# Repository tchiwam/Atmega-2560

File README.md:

# Atmega-2560
Derivative work from the orginal Arduino MEGA 2650 R3 Creative Commons Attribution Share-Alike

# The why
I was simply flexing my kicad skills with the latest version 5.0.0

# The long term goal
This will be the start of a series of adapted Atmega2650 boards for various purposes.

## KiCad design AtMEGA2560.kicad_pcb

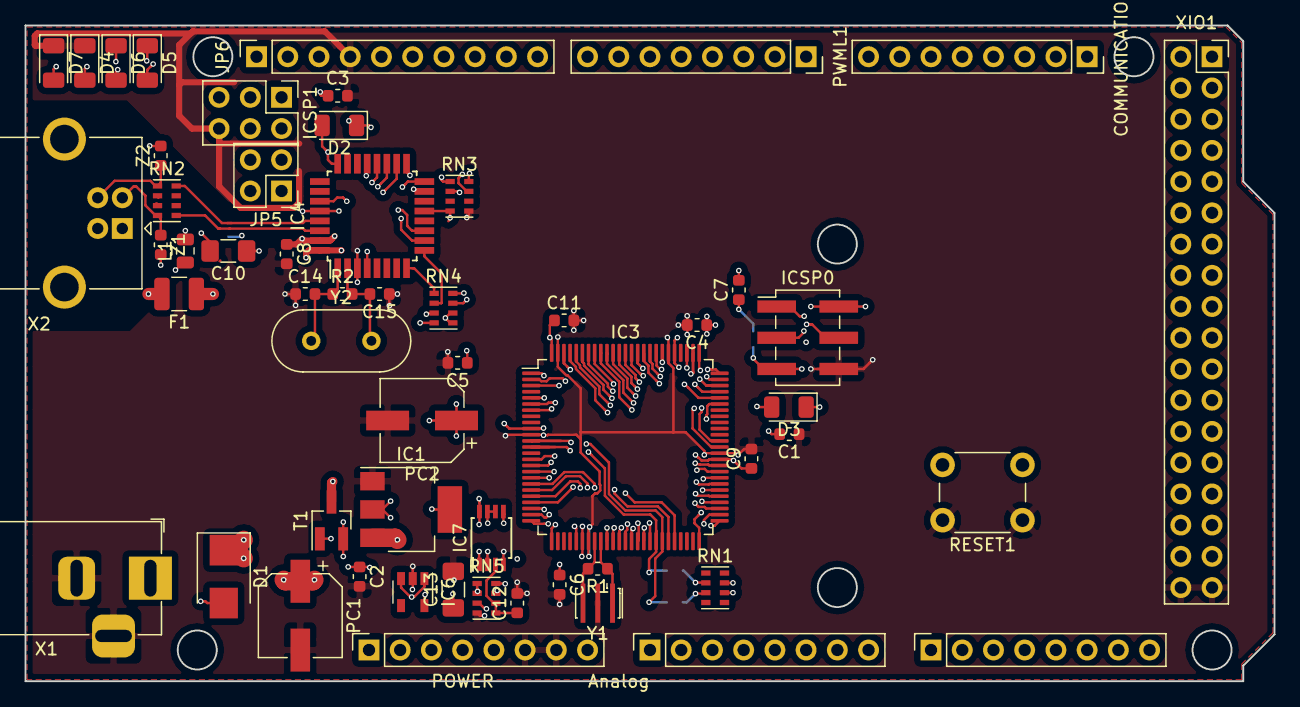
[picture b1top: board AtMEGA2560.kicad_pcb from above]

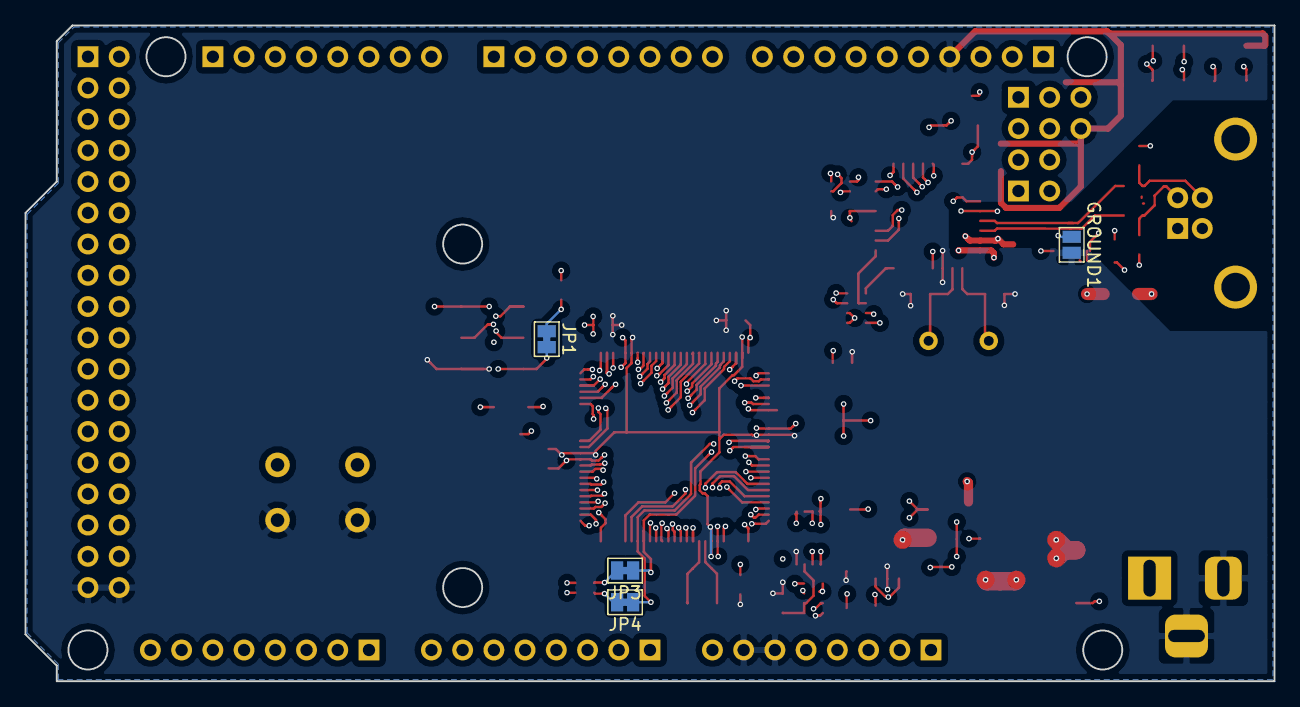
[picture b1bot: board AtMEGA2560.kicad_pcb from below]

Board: 4 copper layers, 101.6 x 53.3 mm, 60 parts (4 on the bottom side), 113 nets.

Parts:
ADCH1: Conn_01x08; PinSocket_1x08_P2.54mm_Vertical
ADCL1: Conn_01x08; PinSocket_1x08_P2.54mm_Vertical
C1, C14, C15: 22pF; C_0603_1608Metric
C2, C4, C5, C6: 100n; C_0603_1608Metric
C3, C7, C8, C9, C11, C12: 100nF; C_0603_1608Metric
C10, C13: 1uF; C_1206_3216Metric_Pad1.42x1.75mm_HandSolder
COMMUNICATION1: Conn_01x08; PinSocket_1x08_P2.54mm_Vertical
D1: M7; D_SMB
D2, D3: CD1206-S01575; D_1206_3216Metric
D4: YEL; LED_1206_3216Metric
D5: RX YELLOW; LED_1206_3216Metric
D6: TX YELLOW; LED_1206_3216Metric
D7: GRN; LED_1206_3216Metric
F1: MF-MSMF050-2 500mA; Fuse_1210_3225Metric
GROUND1: SolderJumper_2_Open; SolderJumper-2_P1.3mm_Open_Pad1.0x1.5mm
IC1: NCP1117-5.0_SOT223; SOT-223-3_TabPin2
IC3: ATmega2560-16AU; TQFP-100_14x14mm_P0.5mm
IC4: ATmega16U2-AU; TQFP-32_7x7mm_P0.8mm
IC6: LP2985-3.3; SOT-23-5
IC7: LMV358IDGKR; TSSOP-8_3x3mm_P0.65mm
ICSP0: Conn_02x03_Odd_Even; PinHeader_2x03_P2.54mm_Vertical_SMD
ICSP1: Conn_02x03_Odd_Even; PinHeader_2x03_P2.54mm_Vertical
JP1: RESET-EN; SolderJumper-2_P1.3mm_Bridged_Pad1.0x1.5mm
JP3, JP4: SolderJumper_2_Bridged; SolderJumper-2_P1.3mm_Bridged_Pad1.0x1.5mm
JP5: Conn_02x02_Odd_Even; PinHeader_2x02_P2.54mm_Vertical
JP6: Conn_01x10; PinSocket_1x10_P2.54mm_Vertical
L1: BLM21; L_0805_2012Metric
PC1: CP; CP_Elec_6.3x5.4
PC2: 47u; CP_Elec_6.3x5.4
POWER1: Conn_01x08; PinSocket_1x08_P2.54mm_Vertical
PWML1: Conn_01x08; PinSocket_1x08_P2.54mm_Vertical
R1, R2: 1M; R_0603_1608Metric
RESET1: SW_Push; SW_PUSH_6mm
RN1, RN5: 10k; R_Cat16-4
RN2: 22R; R_Cat16-4
RN3, RN4: 1k; R_Cat16-4
T1: FDN340P; SOT-23_Handsoldering
X1: DC21MMX; BarrelJack_Horizontal
X2: USB-B_TH; USB_B_OST_USB-B1HSxx_Horizontal
XIO1: Conn_02x18_Odd_Even; PinSocket_2x18_P2.54mm_Vertical
Y1: CSTCE16M0V53-R0 16MHZ; Resonator_SMD_muRata_CSTxExxV-3Pin_3.0x1.1mm_HandSoldering
Y2: 16MHz; Crystal_HC18-U_Vertical
Z1, Z2: CG0603MLC-05E; R_0603_1608Metric

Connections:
+3V3: C13.1, IC6.5, IC7.2, POWER1.4
+5V: C4.1, C5.1, C6.1, C9.1, C11.1, D2.1, D3.1, IC1.2, IC3.10, IC3.31, IC3.61, IC3.80, IC3.100, IC4.4, IC4.32, IC6.1, IC6.3, IC7.8, ICSP0.2, ICSP1.2, PC2.1, POWER1.2, POWER1.5, RN1.6, RN1.7, RN3.1, RN4.5, RN4.6, RN5.1, RN5.2, T1.2, XIO1.1, XIO1.2
+VDC: C2.1, D1.1, IC1.3, PC1.1, POWER1.8, RN5.3
/8PB4: IC4.18, JP5.1
/8PB5: IC4.19, JP5.3
/8PB6: IC4.20, JP5.2
/8PB7: IC4.21, JP5.4
/ADC0: ADCL1.1, IC3.97
/ADC1: ADCL1.2, IC3.96
/ADC2: ADCL1.3, IC3.95
/ADC3: ADCL1.4, IC3.94
/ADC4: ADCL1.5, IC3.93
/ADC5: ADCL1.6, IC3.92
/ADC6: ADCL1.7, IC3.91
/ADC7: ADCL1.8, IC3.90
/ADC8: ADCH1.1, IC3.89
/ADC9: ADCH1.2, IC3.88
/ADC10: ADCH1.3, IC3.87
/ADC11: ADCH1.4, IC3.86
/ADC12: ADCH1.5, IC3.85
/ADC13: ADCH1.6, IC3.84
/ADC14: ADCH1.7, IC3.83
/ADC15: ADCH1.8, IC3.82
/MISO2: IC4.17, ICSP1.1
/MOSI2: IC4.16, ICSP1.4
/PB4: IC3.23, JP6.8
/PB5: IC3.24, JP6.7
/PB6: IC3.25, JP6.6
/PC0: IC3.53, XIO1.17
/PC1: IC3.54, XIO1.18
/PC2: IC3.55, XIO1.15
/PC3: IC3.56, XIO1.16
/PC4: IC3.57, XIO1.13
/PC5: IC3.58, XIO1.14
/PC6: IC3.59, XIO1.11
/PC7: IC3.60, XIO1.12
/PE3: IC3.5, PWML1.6
/PE4: IC3.6, PWML1.3
/PE5: IC3.7, PWML1.4
/RXD1: COMMUNICATION1.3, IC3.45
/SCK2: IC4.15, ICSP1.3
/TXD1: COMMUNICATION1.4, IC3.46
/USB1+: IC4.29, RN2.8
/USB1-: IC4.30, RN2.5
/USB2+: RN2.1, X2.3, Z2.1
/USB2-: RN2.4, X2.2, Z1.1
/USBGND: C10.2, GROUND1.1, IC4.28, L1.2, X2.4
/USBSHIELD: L1.1, X2.5, Z1.2, Z2.2
/VBUS: F1.2, X2.1
/XTAL1: IC3.34, R1.1, Y1.1
/XTAL2: IC3.33, R1.2, Y1.3
AREF: C3.1, IC3.98, JP6.3
GND: C1.1, C2.2, C3.2, C4.2, C5.2, C6.2, C8.2, C9.2, C11.2, C12.2, C13.2, C14.1, C15.1, D4.1, D7.1, GROUND1.2, IC1.1, IC3.11, IC3.32, IC3.62, IC3.81, IC3.99, IC4.3, IC6.2, IC7.4, ICSP0.6, ICSP1.6, JP6.4, PC1.2, PC2.2, POWER1.6, POWER1.7, RESET1.1, RN3.5, RN5.4, X1.2, X1.3, XIO1.35, XIO1.36, Y1.2
MISO: IC3.22, ICSP0.1, XIO1.32
MOSI: IC3.21, ICSP0.4, XIO1.31
unnamed: C7.1, JP1.1
unnamed: C10.1, IC4.27
unnamed: C12.1, IC7.3, RN5.5, RN5.6
unnamed: C14.2, IC4.1, R2.1, Y2.1
unnamed: C15.2, IC4.2, R2.2, Y2.2
unnamed: D1.2, X1.1
unnamed: D4.2, RN3.7
unnamed: D5.1, IC4.10
unnamed: D5.2, RN4.3
unnamed: D6.1, IC4.11
unnamed: D6.2, RN4.4
unnamed: D7.2, RN3.8
unnamed: IC4.8, RN4.1
unnamed: IC4.9, RN4.2
unnamed: IC7.1, T1.1
unnamed: IC7.6, IC7.7, RN3.2
unnamed: JP3.2, RN1.2
unnamed: JP4.2, RN1.3
PA0: IC3.78, XIO1.4
PA1: IC3.77, XIO1.3
PA2: IC3.76, XIO1.6
PA3: IC3.75, XIO1.5
PA4: IC3.74, XIO1.8
PA5: IC3.73, XIO1.7
PA6: IC3.72, XIO1.10
PA7: IC3.71, XIO1.9
PB7: IC3.26, IC7.5, JP6.5
PD7: IC3.50, XIO1.20
PG0: IC3.51, XIO1.21
PG1: IC3.52, XIO1.22
PG2: IC3.70, XIO1.19
PG5: IC3.1, PWML1.5
PH3: IC3.15, PWML1.7
PH4: IC3.16, PWML1.8
PH5: IC3.17, JP6.10
PH6: IC3.18, JP6.9
PL0: IC3.35, XIO1.29
PL1: IC3.36, XIO1.30
PL2: IC3.37, XIO1.27
PL3: IC3.38, XIO1.28
PL4: IC3.39, XIO1.25
PL5: IC3.40, XIO1.26
PL6: IC3.41, XIO1.23
PL7: IC3.42, XIO1.24
RXD0: IC3.2, PWML1.1, RN4.7
RXD2: COMMUNICATION1.5, IC3.12
RXD3: COMMUNICATION1.7, IC3.63
SCK: IC3.20, ICSP0.3, XIO1.34
SCL: COMMUNICATION1.1, IC3.43, JP3.1, JP6.1
SDA: COMMUNICATION1.2, IC3.44, JP4.1, JP6.2
TXD0: IC3.3, PWML1.2, RN4.8
TXD2: COMMUNICATION1.6, IC3.13
TXD3: COMMUNICATION1.8, IC3.64
USBVCC: C8.1, F1.1, IC4.31, T1.3
~HWB~: C7.2, IC4.13, RN3.4
~RESET2~: D2.2, IC4.24, ICSP1.5, RN5.7
~RESET~: C1.2, D3.2, IC3.30, ICSP0.5, JP1.2, POWER1.3, RESET1.2, RN5.8
~SS~: IC3.19, XIO1.33

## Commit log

2018-08-29 All parts in the schematic
2018-08-29 Pin header instead of SMT
2018-09-11 Labeling of components and location of connectors
2018-09-11 IC4 net renaming PBx to 8PBx, PCB components movements to clear space for ethernet
2018-09-11 PCB components movements to clear space for ethernet
2018-09-13 Orthogonal to digital plane analog routing on prefered plane
2018-09-13 More of the digital routing done
2018-09-17 More of the USB-PSU routing done
2018-09-18 Cleaning up around the USB signals and added USB netname for shield and GND
2018-09-19 Initial USB floods
2018-10-07 Moved few parts for better 5VDC plane and moved some signals.
